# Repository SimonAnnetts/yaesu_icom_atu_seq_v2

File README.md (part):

# Yaesu/Icom ATU Sequencer v2

An Arduino Mega 2560 controller that:

- interfaces an **Icom AH-4-type ATU** (or any tuner using the same protocol) to
  a **Yaesu FT-847**. Note: the radio's own [TUNER] button is not used - we have our own button that initiates a tuning cycle and keys the radio as necessary;
- provides **three sequencer outputs per band, for four bands** (HF, 50, 144
  and 430MHz), for preamp and power-amp control;
- provides an **ALC output** that can control the radio's power during the
  tune cycle;
- allows complex **inter-band sequencer and tuner configurations** be defined in
  a **JSON config**;
- allows a **PC control of the radio over CAT**, with none of the tuner and
  sequencer operations getting in the way.

## Aims in detail

1. **Use an Icom AH-4-type ATU with the Yaesu FT-847** (or any tuner that
   speaks the same START/KEY protocol, and possibly other Yaesu radios of the
   same era). 
   The FT-847 has no way to drive such a tuner on its own. At the
   press of the TUNE button the Arduino runs the whole
   cycle: it sets the radio up over CAT (tune mode, keying PTT at the right
   moment), drives the tuner's START/KEY lines, watches for it to finish, and
   puts the radio back as it found it. Proven on an Alinco EDX-2, an
   Icom-compatible tuner. **This does not re-purpose the radio's own [TUNER]
   key** or any of its built-in tuner control: the TUNE button is button 
   fitted to this device (with its own tune indicator), and
   the radio's rear TUNER connector is used only for the TX INHIBIT line and
   its supply and ground. Its tuner-sense pin is deliberately left
   unconnected, so the radio never believes a tuner is attached and CAT keeps
   working.
2. **Provide three sequencer outputs per band, for four bands** (HF, 50, 144
   and 430MHz): `SEQ1`–`SEQ3` opto-isolated outputs for preamp and power-amp
   relays, plus `RX`/`TX` indicator LEDs, driven from the radio's STBY jack,
   with a shared **TX INHIBIT** line that holds off the transmitter until
   each band's sequence has finished settling.
3. **Provide an ALC output that can control the radio's power during the tune
   cycle.** A charge pump makes about -4V, gated by an opto-isolator onto the
   radio's EXT ALC jack, so the carrier is held at what the tuner wants (an
   AH-4 needs about 10W). On the prototype one fixed ALC voltage holds the
   FT-847 between 5 and 10W on every band (once the pump is fed from a
   regulator: see below). YMMV - the Yaesu FT-847 ALC circuit, and the power
   levels it produces, are 'unpredictable' at best! The ALC output is **part
   of every tune by default** (it does no harm if the radio's ALC jack isn't
   connected), and can be switched off per band with `"alc": false` in the JSON
   config.
4. **Allow complex inter-band sequencer and tuner configurations to be defined
   in a JSON config**: per-band delays, tune profiles, band edges, which bands
   the tuner may be used on, and cross-band rules (for example, transmitting
   on 50MHz switches off a 144MHz masthead preamp). The config is uploaded
   over USB, validated, and kept in EEPROM; a bad one can never leave the
   sequencer unable to run.
5. **Still let a PC control the radio over CAT, with none of the above getting
   in the way.** The Arduino sits between the PC and the radio and passes CAT
   traffic through byte for byte. While a tune cycle needs the radio, the PC
   keeps being answered (from a snapshot of the radio, with the original mode
   and no PTT), so it cannot tell a tune is happening.

**The PC is optional.** With no PC connected at all, the tune button, the
tuner and the sequencer all work exactly the same way. Standalone operation is
a first-class requirement, not a side effect.

## How it fits together

```
 PC (flrig etc.) ── Port 1 ──┐                        ┌── CAT ── Port 2 ── FT-847
                             │                        │
                       Arduino Mega 2560 ─────────────┼── STBY jack (4 bands in)
                             │                        ├── TUNER connector: TX INHIBIT out
   tune button ──────────────┤                        └── EXT ALC jack  ←── charge pump + gate
   tune buzzer ──────────────┤
   AH-4-type ATU ─ START/KEY ┤        12 opto outputs (SEQ1-SEQ3 × 4 bands) + RX/TX LEDs
                             └── USB (Serial0): logging, bench keys, JSON config upload
```

The CAT proxy is the *means*, not the goal: it is what lets aims 1 and 5 hold
at the same time (the tune cycle needs the radio's CAT port while the PC is
still using it). The sequencer (aim 2) does not use CAT at all — it runs from
the STBY lines, so it works with the CAT link absent.

Where to look in this document: [Hardware](#hardware) and the
[Pin plan](#pin-plan-mega-2560) for the wiring; [Behaviour](#behaviour) for the tune
cycle, the sequencer and the config; the reference sections for the
[FT-847 CAT protocol](#yaesu-ft-847-cat-protocol-reference), the [AH-4 interface](#icom-ah-4-atu-interface-reference), the
[ALC circuit](#alc-injection-for-tune-power-reference) and the
[STBY jack, TUNER port and TX INHIBIT](#stby-jack-tuner-port-and-tx-inhibit-reference); [Bench results](#bench-results)
for what has been verified on the real radio and tuner; [Open
questions](#open-questions--to-be-determined) for what has not.

## Hardware

- **Arduino Mega 2560** as the controller.
- **Serial0 (USB)**: connected to a PC via USB, used for debugging/logging and
  local control/monitoring of the Arduino itself. Not part of the CAT path.
- **Serial2 ("Port 1")**: connects to the PC's CAT serial port, via one half
  of a MAX202CPE (RS-232 level shifter).
- **Serial3 ("Port 2")**: connects to the Yaesu FT-847's CAT port, via the
  other half of the MAX202CPE.
- **Serial1**: unused, left entirely free — see [pin plan](#pin-plan-mega-2560) below.
- **Icom ATU interface**: drives an Icom-series automatic antenna tuner (e.g.
  AH-4) using its start/key line(s) and tune-complete signalling.
- **Tune button**: a new, separate physical pushbutton added by this device,
  wired to an Arduino input, used to initiate a tune cycle. It has nothing to
  do with the radio's front-panel [TUNER] key, which is not used or
  intercepted.
- **ALC injection circuit**: a charge pump driven from an Arduino PWM pin
  (producing roughly -4V), gated onto the radio's ALC line through an
  opto-isolator used purely as a switch. This lets the Arduino trim the
  radio's RF output to the ~10W carrier the AH-4 wants during a tune cycle
  (it aborts outside 5–15W — see the [AH-4 reference](#icom-ah-4-atu-interface-reference) below), independent
  of — and in addition to — the AM-mode power ceiling (see below). Carried over from a prior project; confirmed against the FT-847
  manual — see the [ALC reference section](#alc-injection-for-tune-power-reference) further down.
- **Amplifier sequencer**: 4 independent relay sequencers, one per band —
  Band 1=HF, Band 2=50MHz, Band 3=144MHz, Band 4=430MHz — each with 5
  distinct outputs —
  `RX`, `SEQ1`, `SEQ2`, `SEQ3`, `TX`. These are cumulative, not mutually
  exclusive: `SEQ1`-`SEQ3` latch on in order and stay on together for the
  whole transmission, while `RX`/`TX` are boundary-condition indicator
  LEDs (see [Sequencer](#sequencer) under [Behaviour](#behaviour) for the exact timing). All 5 drive
  a status LED; only `SEQ1`/`SEQ2`/`SEQ3` also drive an opto-isolator
  (`RX`/`TX` are LED indicators only, no relay/opto function) — 12
  opto-isolator outputs total, 3 per band (see [Pin plan](#pin-plan-mega-2560)). Triggered by the
  radio's STBY jack (4 closure-to-ground T/R lines, wired to the
  interrupt-capable pins — see [Pin plan](#pin-plan-mega-2560)). A single, shared **TX INHIBIT**
  output (D4) holds off the radio's actual transmit output while each
  band's sequence runs, wired to pin 8 of the radio's TUNER connector.
  Also configurable (JSON-based — see below) so that transmitting on one
  band can partially trigger another band's sequencer, e.g. disabling a
  masthead preamp on an unrelated band while transmitting nearby. See
  [Sequencer](#sequencer) under [Behaviour](#behaviour), and the [TUNER-port reference
  section](#stby-jack-tuner-port-and-tx-inhibit-reference) further down for the confirmed pinout and how the CAT-disable
  risk is avoided (by deliberately leaving the TUNER connector's separate
  Tuner Sense pin unconnected).

### Pin plan (Mega 2560)

| Pin(s) | Function |
|---|---|
| D0/D1 (Serial0) | USB debug/control link to PC |
| D16/D17 (Serial2) | Port 1 — CAT to PC, via MAX202CPE |
| D14/D15 (Serial3) | Port 2 — CAT to radio, via MAX202CPE |
| D6 | Tune button (input, polled) |
| D7 | Tune indicator: passive buzzer, ~2048Hz PWM from Timer4 (OC4B) |
| D8 | CAT activity LED (output): lit for 20ms after every byte on either CAT port - the PC's, the radio's, and the Arduino's own commands and replies |
| D9 | ALC injection charge pump (PWM output, Timer2) |
| D10 | ALC opto-isolator LED drive (the "gate"): a plain on/off switch |
| D11 | Icom AH-4 `KEY` input, via opto-isolator, `INPUT_PULLUP` |
| D12 | Icom AH-4 `START` output, via opto-isolator |
| D2 | STBY: HF (input, interrupt) |
| D3 | STBY: 430MHz (input, interrupt) |
| D18 | STBY: 144MHz (input, interrupt) |
| D19 | STBY: 50MHz (input, interrupt) |
| D4 | Shared TX INHIBIT output → TUNER connector pin 8 |
| D34 / D35 / D36 / D37 / D38 | Sequencer Band 1 (**HF**): `RX` (LED only) / `SEQ1` (LED+opto) / `SEQ2` (LED+opto) / `SEQ3` (LED+opto) / `TX` (LED only) |
| D39 / D40 / D41 / D42 / D43 | Sequencer Band 2 (**50MHz**): `RX` / `SEQ1` / `SEQ2` / `SEQ3` / `TX` — same LED-only/LED+opto pattern as Band 1 |
| D44 / D45 / D46 / D47 / D48 | Sequencer Band 3 (**144MHz**): `RX` / `SEQ1` / `SEQ2` / `SEQ3` / `TX` — same pattern |
| D49 / D50 / D51 / D52 / D53 | Sequencer Band 4 (**430MHz**): `RX` / `SEQ1` / `SEQ2` / `SEQ3` / `TX` — same pattern; D50-D53 are the Mega's hardware SPI pins (MISO/MOSI/SCK/SS), repurposed as plain digital outputs since SPI isn't needed elsewhere in this project |
| D5, D22–D33 | **unassigned** — free (D5 was once reserved for the TUNER connector's `TX_GND`, which is not connected; the sequencer outputs occupy D34–D53 as one contiguous block) |
| D20, D21 (I2C: SDA/SCL) | **kept free** — not used by anything, available for a future I2C peripheral (e.g. a status display) |

Sequencer band↔channel mapping (Band 1=HF, Band 2=50MHz, Band 3=144MHz,
Band 4=430MHz) is independent of, and doesn't follow the same order as,
the STBY input pin assignment above (D2=HF, D3=430MHz, D18=144MHz,
D19=50MHz) — each STBY input simply needs to be cross-wired in firmware
to drive its matching band's sequencer channel, e.g. STBY D2 (HF) drives
Band 1 (D34-38), STBY D3 (430MHz) drives Band 4 (D49-53), and so on.

Only six Mega 2560 pins support true external interrupts: D2, D3, D18,
D19, D20, D21. Putting both CAT links on Serial2/Serial3 (rather than
Serial1) means Serial1's pins — D18/D19, which are two of those six
interrupt-capable pins — are never touched, so **all six** interrupt pins
stay free instead of just four. Four of them (D2, D3, D18, D19) are now
used for the 4 STBY band lines (interrupt-driven, since a TX request
needs to be caught immediately to start the sequencer); the remaining two
(D20/D21) stay free of any reservation for I2C. The tune button (D6)
doesn't need an interrupt-capable pin — it's polled in the main loop — so
it and the two status LEDs (D7, D8) sit comfortably outside the reserved
set. The 20 sequencer outputs (D34-D53) and the shared TX INHIBIT output
(D4) are plain digital outputs with no special pin requirements. The
Arduino-side band↔pin mapping for STBY (which of D2/D3/D18/D19
is HF vs 50 vs 144 vs 430) is likewise our own software's choice; what
actually matters is wiring it consistently against the STBY jack's real
per-band wiring (see the [STBY jack reference](#stby-jack-tuner-port-and-tx-inhibit-reference) below).

## Behaviour

### Normal operation (passthrough)

- Bytes arriving on Port 1 (from the PC) are forwarded to Port 2 (to the
  radio), and bytes arriving on Port 2 (from the radio) are forwarded to
  Port 1 (to the PC).
- If no PC is connected, Port 1 simply carries no traffic — there is
  nothing to relay. This is a normal, fully supported state, not an error
  condition; see [Standalone operation](#standalone-operation) below for how the tune cycle still
  works correctly in this case.
- **Power-up resync.** When the Arduino powers up it puts a glitch on the
  radio's serial line (the RS-232 level shifter comes up), which can leave the
  radio's CAT port with CAT off, or with its 5-byte parser out of step by one
  stray byte. flrig's polls arrive back to back, so the radio never gets the
  200ms gap it needs to resync and then never answers (flrig shows no
  communication until Init). So for the first ~0.5s the bridge holds the PC's
  bytes unread in the serial buffer (nothing is lost: it holds about 50
  frames), lets the bus go quiet for 300ms, sends one CAT on, waits 200ms for the
  radio to settle, and only then starts forwarding — the held polls go through
  intact and in order, so the only visible effect is flrig's first answer
  arriving about half a second after power-up. A tune requested in that
  window waits for it. CAT on is idempotent, so a healthy radio is unaffected;
  with the radio off nothing answers and the bridge simply carries on.

### What actually needs faking during a tune cycle

The tune cycle only ever changes two things about the radio's externally
visible state: **mode** (forced to AM) and **PTT/TX status** (forced on).
Frequency doesn't change; CTCSS/DCS/satellite-toggle/etc. don't change;
none of it is touched by tuning. That means the Arduino only ever needs to
fake two specific things, not maintain a general-purpose cache of
"everything the PC might ask":

- **Mode** — the mode byte within the `Get freq+mode, Main` reply
  (opcode `0x03`; see the [CAT reference](#yaesu-ft-847-cat-protocol-reference) below). This reply packs
  frequency and mode into one 5-byte frame, so the Arduino must splice the
  *real, live* frequency (queried from the radio, since it's genuinely
  unchanged) together with the *faked* pre-tune mode byte — not fake the
  whole response.
- **PTT/TX status** — the PTT bit in the `Get TX status` reply
  (opcode `0xF7`).
- Nothing else needs faking. In particular, RX status/S-meter (opcode
  `0xE7`) can be forwarded live and truthfully even while keyed — a
  receiver being blind during any transmission (including an entirely
  ordinary, manually-initiated one) is unremarkable and gives nothing
  away.
- **Any CAT query the Arduino doesn't specifically recognise is simply
  forwarded to the radio and its response forwarded back, live, even
  during a tune cycle.** There is no cache-completeness problem to solve —
  a query the Arduino has never seen before isn't one it needs to fake an
  answer for, because the radio itself can truthfully answer it regardless
  of whether it's mid-tune. Pre-populating an exhaustive cache of "every
  possible CAT parameter" is unnecessary; only the two items above ever
  diverge from the truth.

### Tune cycle (triggered by the tune button)

The tune cycle must also drive the amplifier sequencer for whichever band
it's about to transmit on — a tune cycle keys PTT just like any other
transmission, and the sequencer's relay chain has to be up before RF
appears, exactly as it would for a normal transmission.

A CAT-commanded PTT does assert the radio's STBY line(s) (bench-verified —
see [Bench results](#bench-results) below), but the lead time before RF is still unmeasured.
Rather than depend on that, the tune cycle **explicitly drives the
sequencer itself**, calling the same up/down-sequence logic the STBY
interrupt handler uses, directly and proactively:

1. Actively query the radio's current mode and frequency over CAT
   (`Get freq+mode, Main`, opcode `0x03`) and note the current PTT/TX
   status is "off" (this is always known without needing to ask, since
   the Arduino is the one about to turn it on). This captures the values
   that will need to be faked and restored, freshly, at the start of
   every cycle — so it works identically whether or not a PC (and any
   snooped history) exists.
2. Map that frequency to one of the 4 sequencer bands (see [Sequencer
   configuration](#sequencer-configuration-and-cross-band-triggers) below — band edges live in the same JSON config).
3. **Explicitly run that band's *tune* profile up-sequence first, before
   touching the AH-4 at all** — assert TX INHIBIT, step through whichever
   stages the tune profile includes for this band (may stop at `SEQ2`,
   skipping `SEQ3` — see "Two profiles per band" under [Sequencer](#sequencer) above),
   release TX INHIBIT — using the same function the STBY interrupt handler
   calls, but with the tune profile rather than the normal-TX profile.
   - **This band's STBY interrupt handling must be suppressed for the
     duration of the tune cycle.** The idempotency argument used elsewhere
     (calling "run up-sequence" again on an already-sequenced band is a
     harmless no-op) only holds when both callers agree on the same
     profile. Here they don't: if the radio's own STBY line asserts once
     PTT goes active and the interrupt handler fires using the *normal*
     profile, it would engage `SEQ3` anyway — exactly what the tune
     profile exists to prevent. So the tune cycle needs to mark this band
     as "under explicit tune-profile control" and have the STBY handler
     defer to it (skip its own trigger) until the tune cycle releases
     that band again in step 9.
   - **Ordering also matters here**: this step is deliberately done
     *before* issuing the AH-4 `START` signal (step 5), not interleaved
     with it.
     The AH-4 has its own tight timing — it asserts `KEY` about 300ms
     after `START`, then expects the carrier almost immediately so it can
     check the power — and the sequencer's relay-settling delay is
     user-configurable and could easily be longer than that. Running the
     sequencer to completion first, while the radio is still fully idle,
     keeps that variable delay out of the AH-4's time-sensitive window
     entirely, so `START → KEY → PTT-key → RF appears` stays a tight,
     undisturbed sequence exactly as the AH-4 expects.
4. Take over the CAT link to the radio and select AM mode (there is no CAT
   power-set command on this radio — switching to AM mode is itself the
   main power reduction, since the FT-847 caps AM output much lower than
   SSB/CW/FM; see the [CAT reference](#yaesu-ft-847-cat-protocol-reference) below). **The target is about 10W, not
   the minimum:** the AH-4 measures the carrier during the tune and aborts
   if it is outside 5–15W (see the [AH-4 reference](#icom-ah-4-atu-interface-reference) below). AM mode alone
   still allows up to 25W on HF, so the radio's RF power setting and/or the
   ALC injection circuit must bring the carrier into that window. ALC
   injection is on by default for every band (the config's per-band `alc`
   flag can turn it off, and the no-RF test modes never use it): it is applied
   right after the mode is set — the gate switches the charge pump's -4V onto
   the radio's ALC line and is given 100ms to settle — before `START` and
   before the radio is keyed (see [ALC in the firmware](#alc-in-the-firmware-srcalc_ioh)).
   Also claim the CAT bus now (hold PC traffic) so that PTT can go out the
   instant `KEY` asserts, rather than queueing behind a PC poll.
5. Assert `START` (pull it low via its opto), hold it for about 560ms like
   an Icom radio does, then release it. **Key the radio's PTT via CAT right
   away, at `START`, not later at `KEY`.** The radio's carrier overshoots to
   2–3× its set power for ~0.7s after keying and an Alinco EDX-2 that is only
   given RF at `KEY` measures that overshoot, gives up after ≈350ms and
   leaves the SWR >3:1; keyed at `START` the carrier has settled by the time
   `KEY` asserts (≈590ms) and the tune runs 3–4s and ends near 1:1. The cost
   is a few hundred ms of carrier into the unmatched antenna before `KEY`,
   which is acceptable at ~10W (a genuine AH-4 would route RF through its
   power divider only after `KEY`; the key-on-`KEY` variant, Serial0 `R`, is
   kept for tuners that need that). Meanwhile, continue forwarding any other
   CAT traffic between PC and radio live (see above) — only mode and PTT/TX
   status queries get answered from the values captured in step 1 instead
   of the truth.
6. Wait for the tuner to assert `KEY` (during the `START` hold on a genuine
   AH-4, ~35ms after `START` is released on the Alinco EDX-2); give up as
   "no ATU" if it never does (and unkey).
7. Wait for the ATU to signal that its tune cycle has completed: `KEY`
   releasing and staying released is success; `KEY` releasing for ~20ms,
   re-asserting for ~200ms, then releasing is the AH-4's "not tuned"
   signal. (A short `KEY` is not necessarily a failure: an EDX-2 with a
   stored match for the frequency finishes quickly, and the match only
   shows in the SWR on the next key-up. The log shows how long `KEY` was
   asserted; the real judge is the SWR afterwards.)
8. Unkey the radio's PTT **immediately on `KEY`'s first release** (the
   tuner never switches its relays under power, and an Icom radio stops
   transmitting the moment `KEY` goes away). If ALC injection is on, its
   gate is released as soon as the radio is unkeyed.
9. Restore the radio's original mode (from the value captured in step 1;
   retried up to 3 times, and a failure is reported loudly on Serial0), then
   release the CAT bus so PC traffic can flow again.
10. **Explicitly run that band's *tune* profile down-sequence** — the
    mirror of step 3, stepping down through whatever stages the tune
    profile actually engaged. Once complete, release this band from
    "under explicit tune-profile control" so its STBY interrupt handling
    resumes normally.
11. Resume normal passthrough with no faking.

#### Implementation notes (`src/tune.h`, `src/tune_io.cpp`)

- **One tail for every outcome.** Success, refusal, failure, button abort and
  the 30s watchdog all unwind through the same tail — PTT off (retried until
  the radio has been told), restore mode, release the bus, sequencer down,
  drop the STBY hold, wait for START to finish its hold — so no path can
  skip a cleanup step. It is a pure state machine tested against a fake
  radio and a fake tuner (both an EDX-2-style and a genuine-AH-4-style
  timing) with failures injected at every step and an abort swept across the
  whole cycle.
- **The cycle owns the CAT bus** from before `START` until the restore: the
  arbiter's claim lets PTT go out without queueing behind PC traffic. The PC
  is not locked out meanwhile — it is answered from a snapshot (see [PC
  transparency during a tune cycle](#pc-transparency-during-a-tune-cycle)). A claim also releases itself after 60s
  so the PC can never be locked out.
- **ALC injection is part of the cycle, on by default.** When the tuned band's
  config has `alc` on (the default), the cycle has an extra `Alc` step between
  setting the mode and starting the tuner, and releases the gate in the tail
  right after PTT off on every path (tested: never left on after a failure, an
  abort at any moment, or a stuck PTT off). The radio does not currently
  respond to the ALC voltage, so for now it changes nothing, and the tune does
  not depend on it.
- **A radio that does not answer is woken up, not given up on at once.** After
  the Arduino itself has been power-cycled the radio may stop answering CAT (its
  CAT is off, or its 5-byte parser has been left out of step by a stray byte, and
  a PC polling back to back never gives it the 200ms gap it needs to resync). flrig
  then shows no communication until Init, and the tune button used to fail with
  "could not claim the CAT bus" (the PC's polls of the silent radio kept the bus
  looking busy). Now the claim succeeds, and if the first status query gets no
  answer the cycle goes quiet for 300ms, sends CAT on again, lets the radio settle
  for 200ms and asks again, twice, before failing with "CAT query failed". The
  normal path is unchanged (one CAT on, straight to the queries). A successful
  tune leaves the radio's parser aligned, so flrig recovers too.
- **Refusals** (nothing is left changed): a band already transmitting, the
  radio reporting it is transmitting, a frequency in no band, a band the AH-4
  isn't enabled for (the config's per-band `atu` flag), no usable
  answer to a CAT query (including a mode byte that couldn't be restored).
- **CAT activity LED (D8):** lights for 20ms after every byte seen on either CAT
  port, so it flickers with flrig's polling and glows steadily when traffic is
  dense. It counts the PC's bytes (forwarded to the radio, or read while a tune
  has the radio), the radio's bytes (forwarded to the PC, or replies to the
  Arduino's own commands, or strays), the Arduino's own commands, commands
  replayed after a tune, and the recovery commands sent at boot - so a
  standalone tune with no PC still lights it. It is off at boot and with no
  traffic, and the walk-test's `ACTIVITY_LED` step drives it directly.
- **Tune indicator (D7, a passive buzzer):** driven at ~2048Hz by Timer4's
  hardware PWM (not `tone()`, which would take Timer2 from the ALC pump). A
  continuous tone while a cycle runs; three slow beeps on success; fast
  beeping for about a second on failure or refusal; silent after an abort.
  A low-resistance magnetic buzzer must not be driven straight from the pin
  (a 40Ω coil would draw ~125mA against the Mega's 40mA absolute maximum): put
  about **330Ω** in series (~13mA peak, moderate volume; 1kΩ is very quiet,
  not below ~220Ω), optionally a 1N4148 across the buzzer (cathode to the
  pin side), or use a transistor for more volume. `BUZZER_DUTY_PERCENT` in
  `src/buzzer.cpp` is a software volume control.
- **Controls:** the tune button starts a full tune and, pressed during one,
  aborts it. Serial0 keys: `T` full tune, `E` ATU handshake with the radio
  *not* keyed, `D` dry run (sequencer and AM mode only — no ATU, no RF), `M`
  full tune that also logs the radio's PO/ALC meter (about every 60ms while
  keyed; a diagnostic that can delay PTT off by up to ~100ms, so use it at low
  power only), `P` carrier test (keys the radio for 2s with *no* tuner and
  logs the meter — shows the radio's own start-up behaviour on its own), `R`
  full tune that keys the radio at `START` instead of at `KEY` (so the radio's
  start-up overshoot, below, has settled before the tuner measures), `1`/`2`/`3`
  tune mode AM/FM/CW (default AM), `X` abort. The FT-847 cannot report SWR over CAT, and its status byte is a
  5-bit bar-graph value (not calibrated watts), so SWR and real power need
  external meters.
- **Staged bench procedure** (dummy load, low power): `D` first (check the
  sequencer steps up with the tune profile, the radio goes to AM and comes
  back), then `E` (START/KEY with the real tuner but no carrier — expect "not
  a real tune"), then `T` into a dummy load with the radio's power set for
  about 10W, then onto the antenna.

### Reset safety (watchdog and crash recovery)

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
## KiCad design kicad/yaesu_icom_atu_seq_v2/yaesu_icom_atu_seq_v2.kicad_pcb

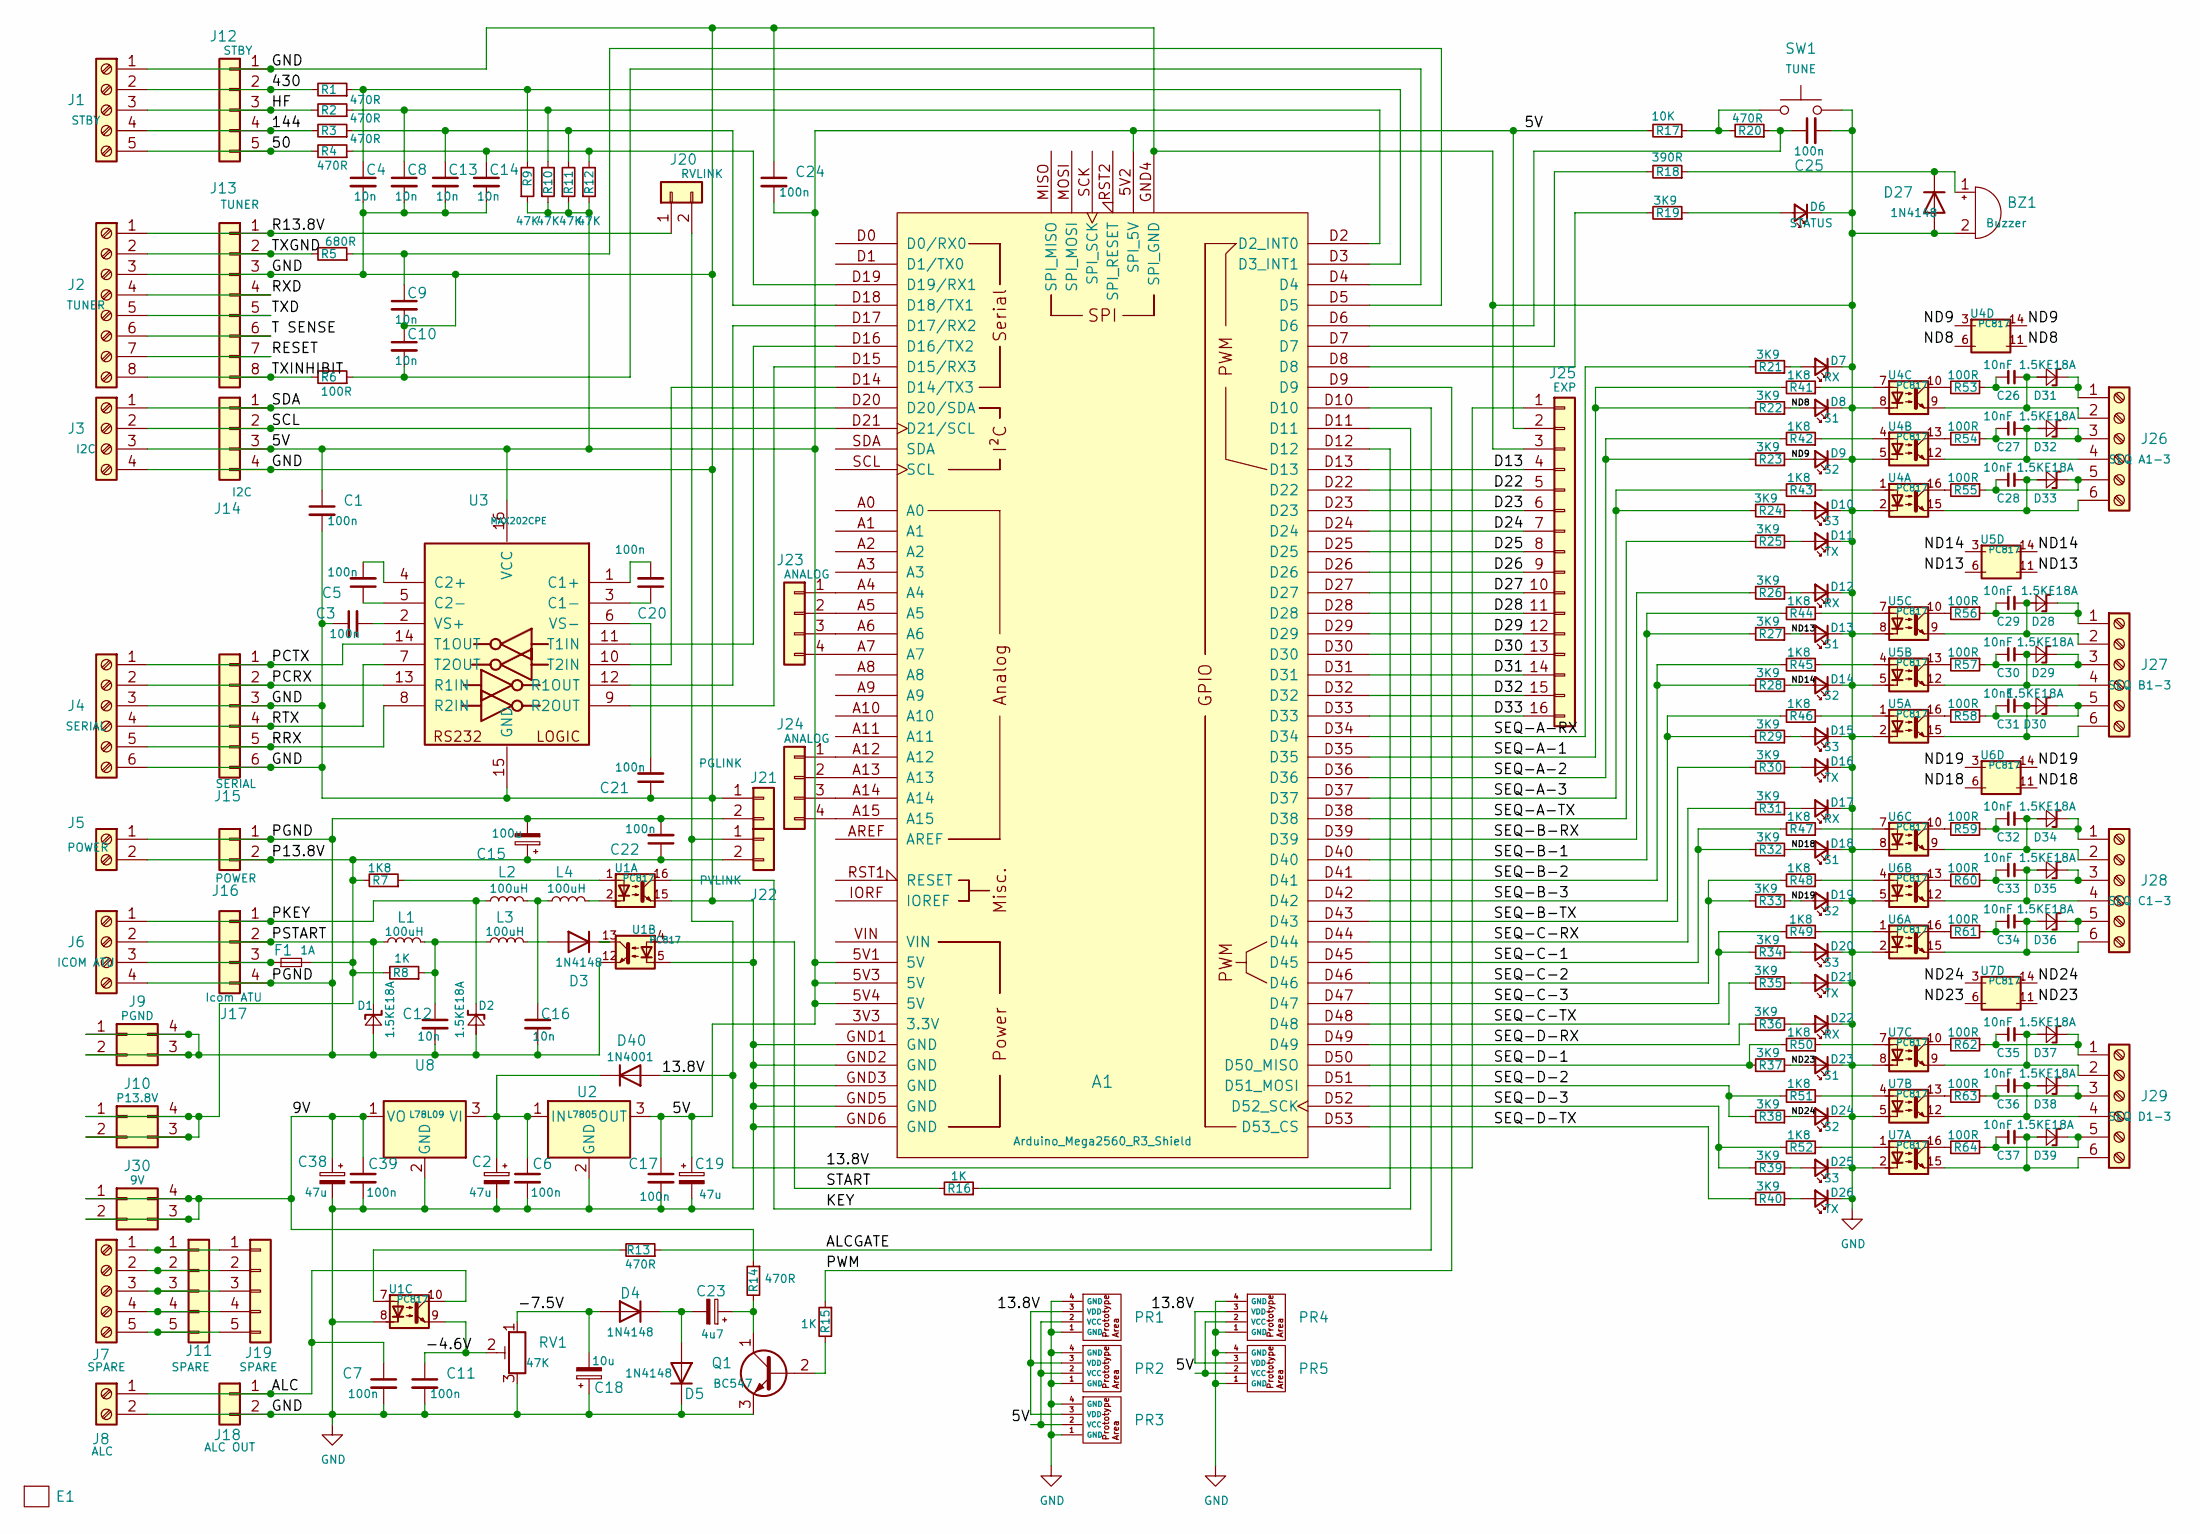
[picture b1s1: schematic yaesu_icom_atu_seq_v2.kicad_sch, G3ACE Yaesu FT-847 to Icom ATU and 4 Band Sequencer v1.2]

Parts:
A1: Arduino_Mega2560_R3_Shield
BZ1: Buzzer; Buzzer_12x9.5RM7.6
C1, C3, C5, C6, C7, C11, C17, C20, C21, C22, C24, C25, C39: 100n; C_Disc_D4.3mm_W1.9mm_P5.00mm
C2, C19, C38: 47u; CP_Radial_D5.0mm_P2.50mm
C4, C8, C9, C10, C12, C13, C14, C16: 10n; C_Disc_D4.3mm_W1.9mm_P5.00mm
C15: 100u; CP_Radial_D5.0mm_P2.50mm
C18: 10u; CP_Radial_D5.0mm_P2.50mm
C23: 4u7; CP_Radial_D5.0mm_P2.50mm
C26, C27, C28, C29, C30, C31, C32, C33, C34, C35, C36, C37: 10nF; C_Disc_D5.1mm_W3.2mm_P5.00mm
D1, D2, D28, D29, D30, D31, D32, D33, D34, D35, D36, D37, D38, D39: 1.5KE18A; D_DO-201AE_P15.24mm_Horizontal
D3, D4, D5, D27: 1N4148; D_DO-35_SOD27_P7.62mm_Horizontal
D6: STATUS; LED_THT_L72CB_Kingbright
D7, D12, D17, D22: RX; LED_THT_L72CB_Kingbright
D8, D13, D18, D23: S1; LED_THT_L72CB_Kingbright
D9, D14, D19, D24: S2; LED_THT_L72CB_Kingbright
D10, D15, D20, D25: S3; LED_THT_L72CB_Kingbright
D11, D16, D21, D26: TX; LED_THT_L72CB_Kingbright
D40: 1N4001; D_DO-35_SOD27_P7.62mm_Horizontal
E1: Hammond_Enclosure_RM2095L
F1: 1A; Fuse_Blade_ATO_directSolder (longer holes)
J1: STBY; TerminalBlock_Phoenix_PT-1,5-5-3.5-H_1x05_P3.50mm_Horizontal
J2: TUNER; TerminalBlock_Phoenix_PT-1,5-8-3.5-H_1x08_P3.50mm_Horizontal
J3: I2C; TerminalBlock_Phoenix_PT-1,5-4-3.5-H_1x04_P3.50mm_Horizontal
J4: SERIAL; TerminalBlock_Phoenix_PT-1,5-6-3.5-H_1x06_P3.50mm_Horizontal
J5: POWER; TerminalBlock_Phoenix_PT-1,5-2-3.5-H_1x02_P3.50mm_Horizontal
J6: ICOM ATU; TerminalBlock_Phoenix_PT-1,5-4-3.5-H_1x04_P3.50mm_Horizontal
J7: SPARE; TerminalBlock_Phoenix_PT-1,5-5-3.5-H_1x05_P3.50mm_Horizontal
J8: ALC; TerminalBlock_Phoenix_PT-1,5-2-3.5-H_1x02_P3.50mm_Horizontal
J9: PGND; PinHeader_2x02_P2.54mm_Vertical
J10: P13.8V; PinHeader_2x02_P2.54mm_Vertical
J11, J19: SPARE; PinHeader_1x05_P2.54mm_Vertical
J12: STBY; PinHeader_1x05_P2.54mm_Vertical
J13: TUNER; PinHeader_1x08_P2.54mm_Vertical
J14: I2C; PinHeader_1x04_P2.54mm_Vertical
J15: SERIAL; PinHeader_1x06_P2.54mm_Vertical
J16: POWER; PinHeader_1x02_P2.54mm_Vertical
J17: Icom ATU; PinHeader_1x04_P2.54mm_Vertical
J18: ALC OUT; PinHeader_1x02_P2.54mm_Vertical
J20: RVLINK; PinHeader_1x02_P2.54mm_Vertical
J21: PGLINK; PinHeader_1x02_P2.54mm_Vertical
J22: PVLINK; PinHeader_1x02_P2.54mm_Vertical
J23, J24: ANALOG; PinHeader_1x04_P2.54mm_Vertical
J25: EXP; PinHeader_1x16_P2.54mm_Vertical
J26: SEQ A1-3; TerminalBlock_Phoenix_PT-1,5-6-3.5-H_1x06_P3.50mm_Horizontal
J27: SEQ B1-3; TerminalBlock_Phoenix_PT-1,5-6-3.5-H_1x06_P3.50mm_Horizontal
J28: SEQ C1-3; TerminalBlock_Phoenix_PT-1,5-6-3.5-H_1x06_P3.50mm_Horizontal
J29: SEQ D1-3; TerminalBlock_Phoenix_PT-1,5-6-3.5-H_1x06_P3.50mm_Horizontal
J30: 9V; PinHeader_2x02_P2.54mm_Vertical
L1, L2, L3, L4: 100uH; L_Axial_L9.5mm_D4.0mm_P5.08mm_Vertical_Fastron_SMCC
PR1, PR2, PR3, PR4, PR5: Prototype Area 5x13 with 4 rails (5x17) 2.54mm Grid
Q1: BC547; TO-92L_Wide
R1, R2, R3, R4, R13, R14, R20: 470R; R_Axial_DIN0207_L6.3mm_D2.5mm_P10.16mm_Horizontal
R5: 680R; R_Axial_DIN0207_L6.3mm_D2.5mm_P10.16mm_Horizontal
R6, R53, R54, R55, R56, R57, R58, R59, R60, R61, R62, R63, R64: 100R; R_Axial_DIN0207_L6.3mm_D2.5mm_P10.16mm_Horizontal
R7, R41, R42, R43, R44, R45, R46, R47, R48, R49, R50, R51, R52: 1K8; R_Axial_DIN0207_L6.3mm_D2.5mm_P10.16mm_Horizontal
R8, R15, R16: 1K; R_Axial_DIN0207_L6.3mm_D2.5mm_P10.16mm_Horizontal
R9, R10, R11, R12: 47K; R_Axial_DIN0207_L6.3mm_D2.5mm_P10.16mm_Horizontal
R17: 10K; R_Axial_DIN0207_L6.3mm_D2.5mm_P10.16mm_Horizontal
R18: 390R; R_Axial_DIN0207_L6.3mm_D2.5mm_P10.16mm_Horizontal
R19, R21, R22, R23, R24, R25, R26, R27, R28, R29, R30, R31, R32, R33, R34, R35, R36, R37, R38, R39, R40: 3K9; R_Axial_DIN0207_L6.3mm_D2.5mm_P10.16mm_Horizontal
RV1: 47K; Potentiometer_Bourns_3296W_Vertical
SW1: TUNE; SW_PUSH-12mm
U1, U4, U5, U6, U7: PC817; 3 x PC817 on a DIP-16_W7.62mm_Socket_LongPads
U2: L7805; TO-220-3_Horizontal_TabDown
U3: MAX202CPE; DIP-16_W7.62mm_Socket_LongPads
U8: L78L09; TO-92_Inline

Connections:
/5V: A1.5V1 (5V), A1.5V2 (SPI_5V), A1.5V3 (5V), A1.5V4 (5V), C1.1, C17.1, C19.1, C24.2, J3.3, J14.3, J25.2, PR1.2 (VCC), PR2.2 (VCC), PR3.2 (VCC), PR4.2 (VCC), PR5.2 (VCC), R9.1, R10.1, R11.1, R12.1, R17.2, U2.3 (OUT), U3.16 (VCC)
/9V: C38.1, C39.1, J30.1, J30.2, J30.3, J30.4, R14.1, U8.1 (VO)
/13.8V: D40.2 (A), J20.2, J22.1, J25.1, PR1.3 (VDD), PR2.3 (VDD), PR3.3 (VDD), PR4.3 (VDD), PR5.3 (VDD)
/50: J1.5, J12.5, R4.2
/144: J1.4, J12.4, R3.2
/430: J1.2, J12.2, R1.2
/-4.6V: C11.1, RV1.2, U1.9
/-7.5V: C18.2, D4.2 (A), RV1.1
/ALC: C7.1, J8.1, J18.1, U1.10
/ALCGATE: A1.D10, R13.1
/D13: A1.D13, J25.4, PR1.30
/D22: A1.D22, J25.5, PR1.29
/D23: A1.D23, J25.6, PR1.28
/D24: A1.D24, J25.7, PR1.27
/D25: A1.D25, J25.8, PR1.26
/D26: A1.D26, J25.9, PR1.25
/D27: A1.D27, J25.10, PR1.24
/D28: A1.D28, J25.11, PR1.23
/D29: A1.D29, J25.12, PR1.22
/D30: A1.D30, J25.13, PR1.21
/D31: A1.D31, J25.14, PR1.20
/D32: A1.D32, J25.15, PR1.19
/D33: A1.D33, J25.16, PR1.18
/HF: J1.3, J12.3, R2.2
/KEY: A1.D11, U1.16
/ND8: D8.2 (A), R22.1, U4.6, U4.11
/ND9: D9.2 (A), R23.1, U4.3, U4.14
/ND13: D13.2 (A), R27.1, U5.6, U5.11
/ND14: D14.2 (A), R28.1, U5.3, U5.14
/ND18: D18.2 (A), R32.1, U6.6, U6.11
/ND19: D19.2 (A), R33.1, U6.3, U6.14
/ND23: D23.2 (A), R37.1, U7.6, U7.11
/ND24: D24.2 (A), R38.1, U7.3, U7.14
/P13.8V: C15.1, C22.1, F1.2, J5.2, J10.1, J10.2, J10.3, J10.4, J16.2, J22.2, R7.2, R8.2
/PCRX: J4.2, J15.2, U3.13 (R1IN)
/PCTX: J4.1, J15.1, U3.14 (T1OUT)
/PGND: C12.2, C15.2, C16.2, C22.2, D1.2 (A2), D2.2 (A2), J5.1, J6.4, J9.1, J9.2, J9.3, J9.4, J16.1, J17.4, J21.2, U1.12
/PKEY: D2.1 (A1), J6.1, J17.1, L2.1
/PSTART: D1.1 (A1), J6.2, J17.2, L1.1
/PWM: A1.D9, R15.1
/R13.8V: J2.1, J13.1, J20.1
/RESET: J2.7, J13.7
/RRX: J4.5, J15.5, U3.8 (R2IN)
/RTX: J4.4, J15.4, U3.7 (T2OUT)
/RXD: J2.4, J13.4
/SCL: A1.D21 (D21/SCL), J3.2, J14.2
/SDA: A1.D20 (D20/SDA), J3.1, J14.1
/SEQ-A-1: A1.D35, R22.2, R41.2
/SEQ-A-2: A1.D36, R23.2, R42.2
/SEQ-A-3: A1.D37, R24.2, R43.2
/SEQ-A-RX: A1.D34, R21.2
/SEQ-A-TX: A1.D38, R25.2
/SEQ-B-1: A1.D40, R27.2, R44.2
/SEQ-B-2: A1.D41, R28.2, R45.2
/SEQ-B-3: A1.D42, R29.2, R46.2
/SEQ-B-RX: A1.D39, R26.2
/SEQ-B-TX: A1.D43, R30.2
/SEQ-C-1: A1.D45, R32.2, R47.2
/SEQ-C-2: A1.D46, R33.2, R48.2
/SEQ-C-3: A1.D47, R34.2, R49.2
/SEQ-C-RX: A1.D44, R31.2
/SEQ-C-TX: A1.D48, R35.2
/SEQ-D-1: A1.D50 (D50_MISO), R37.2, R50.2
/SEQ-D-2: A1.D51 (D51_MOSI), R38.2, R51.2
/SEQ-D-3: A1.D52 (D52_SCK), R39.2, R52.2
/SEQ-D-RX: A1.D49, R36.2
/SEQ-D-TX: A1.D53 (D53_CS), R40.2
/START: R16.2, U1.4
/T SENSE: J2.6, J13.6
/TXD: J2.5, J13.5
/TXGND: J2.2, J13.2, R5.2
/TXINHIBIT: J2.8, J13.8, R6.2
GND: A1.GND1 (GND), A1.GND2 (GND), A1.GND3 (GND), A1.GND4 (SPI_GND), A1.GND5 (GND), A1.GND6 (GND), BZ1.2 (-), C1.2, C2.2, C3.1, C4.2, C6.2, C7.2, C8.2, C9.2, C10.1, C11.2, C13.2, C14.2, C17.2, C18.1, C19.2, C21.1, C24.1, C25.2, C38.2, C39.2, D5.1 (K), D6.1 (K), D7.1 (K), D8.1 (K), D9.1 (K), D10.1 (K), D11.1 (K), D12.1 (K), D13.1 (K), D14.1 (K), D15.1 (K), D16.1 (K), D17.1 (K), D18.1 (K), D19.1 (K), D20.1 (K), D21.1 (K), D22.1 (K), D23.1 (K), D24.1 (K), D25.1 (K), D26.1 (K), D27.2 (A), J1.1, J2.3, J3.4, J4.3, J4.6, J8.2, J12.1, J13.3, J14.4, J15.3, J15.6, J18.2, J21.1, J25.3, PR1.1 (GND), PR1.4 (GND), PR2.1 (GND), PR2.4 (GND), PR3.1 (GND), PR3.4 (GND), PR4.1 (GND), PR4.4 (GND), PR5.1 (GND), PR5.4 (GND), Q1.3 (E), RV1.3, SW1.2, U1.5, U1.8, U1.15, U2.2 (GND), U3.15 (GND), U4.2, U4.5, U4.8, U5.2, U5.5, U5.8, U6.2, U6.5, U6.8, U7.2, U7.5, U7.8, U8.2 (GND)
unnamed: A1.D2 (D2_INT0), C8.1, R2.1, R10.2
unnamed: A1.D3 (D3_INT1), C4.1, R1.1, R9.2
unnamed: A1.D14 (D14/TX3), U3.10 (T2IN)
unnamed: A1.D15 (D15/RX3), U3.9 (R2OUT)
unnamed: A1.D16 (D16/TX2), U3.11 (T1IN)
unnamed: A1.D17 (D17/RX2), U3.12 (R1OUT)
unnamed: A1.D18 (D18/TX1), C13.1, R3.1, R11.2
unnamed: A1.D19 (D19/RX1), C14.1, R4.1, R12.2
unnamed: A1.D4, C10.2, R6.1
unnamed: A1.D5, C9.1, R5.1
unnamed: A1.D6, C25.1, R20.1
unnamed: A1.D7, R18.2
unnamed: A1.D8, R19.2
unnamed: A1.D12, R16.1
unnamed: BZ1.1 (+), D27.1 (K), R18.1
unnamed: C12.1, L1.2, L3.2, R8.1
unnamed: C16.1, L2.2, L4.2
unnamed: D3.2 (A), L3.1
unnamed: D3.1 (K), U1.13
unnamed: C23.2, D4.1 (K), D5.2 (A)
unnamed: D6.2 (A), R19.1
unnamed: D7.2 (A), R21.1
unnamed: D10.2 (A), R24.1
unnamed: D11.2 (A), R25.1
unnamed: D12.2 (A), R26.1
unnamed: D15.2 (A), R29.1
unnamed: D16.2 (A), R30.1
unnamed: D17.2 (A), R31.1
unnamed: D20.2 (A), R34.1
unnamed: D21.2 (A), R35.1
unnamed: D22.2 (A), R36.1
unnamed: D25.2 (A), R39.1
unnamed: D26.2 (A), R40.1
unnamed: C29.2, D28.1 (A1), J27.1, R56.1
unnamed: C29.1, D28.2 (A2), J27.2, U5.9
unnamed: C30.2, D29.1 (A1), J27.3, R57.1
unnamed: C30.1, D29.2 (A2), J27.4, U5.12
unnamed: C31.2, D30.1 (A1), J27.5, R58.1
unnamed: C31.1, D30.2 (A2), J27.6, U5.15
unnamed: C26.2, D31.1 (A1), J26.1, R53.1
unnamed: C26.1, D31.2 (A2), J26.2, U4.9
unnamed: C27.2, D32.1 (A1), J26.3, R54.1
unnamed: C27.1, D32.2 (A2), J26.4, U4.12
unnamed: C28.2, D33.1 (A1), J26.5, R55.1
unnamed: C28.1, D33.2 (A2), J26.6, U4.15
unnamed: C32.2, D34.1 (A1), J28.1, R59.1
unnamed: C32.1, D34.2 (A2), J28.2, U6.9
unnamed: C33.2, D35.1 (A1), J28.3, R60.1
unnamed: C33.1, D35.2 (A2), J28.4, U6.12
unnamed: C34.2, D36.1 (A1), J28.5, R61.1
unnamed: C34.1, D36.2 (A2), J28.6, U6.15
unnamed: C35.2, D37.1 (A1), J29.1, R62.1
unnamed: C35.1, D37.2 (A2), J29.2, U7.9
unnamed: C36.2, D38.1 (A1), J29.3, R63.1
unnamed: C36.1, D38.2 (A2), J29.4, U7.12
unnamed: C37.2, D39.1 (A1), J29.5, R64.1
unnamed: C37.1, D39.2 (A2), J29.6, U7.15
unnamed: C2.1, C6.1, D40.1 (K), U2.1 (IN), U8.3 (VI)
unnamed: J7.1, J11.1, J19.1
unnamed: J7.2, J11.2, J19.2
unnamed: J7.3, J11.3, J19.3
unnamed: J7.4, J11.4, J19.4
unnamed: J7.5, J11.5, J19.5
unnamed: F1.1, J6.3, J17.3
unnamed: A1.A4, J23.1
unnamed: A1.A5, J23.2
unnamed: A1.A6, J23.3
unnamed: A1.A7, J23.4
unnamed: A1.A12, J24.1
unnamed: A1.A13, J24.2
unnamed: A1.A14, J24.3
unnamed: A1.A15, J24.4
unnamed: L4.1, U1.2
unnamed: Q1.2 (B), R15.2
unnamed: C23.1, Q1.1 (C), R14.2
unnamed: R7.1, U1.1
unnamed: R13.2, U1.7
unnamed: R17.1, R20.2, SW1.1
unnamed: R41.1, U4.7
unnamed: R42.1, U4.4
unnamed: R43.1, U4.1
unnamed: R44.1, U5.7
unnamed: R45.1, U5.4
unnamed: R46.1, U5.1
unnamed: R47.1, U6.7
unnamed: R48.1, U6.4
unnamed: R49.1, U6.1
unnamed: R50.1, U7.7
unnamed: R51.1, U7.4
unnamed: R52.1, U7.1
unnamed: R53.2, U4.10
unnamed: R54.2, U4.13
unnamed: R55.2, U4.16
unnamed: R56.2, U5.10
unnamed: R57.2, U5.13
unnamed: R58.2, U5.16
unnamed: R59.2, U6.10
unnamed: R60.2, U6.13
unnamed: R61.2, U6.16
unnamed: R62.2, U7.10
unnamed: R63.2, U7.13
unnamed: R64.2, U7.16
unnamed: C20.2, U3.1 (C1+)
unnamed: C20.1, U3.3 (C1-)
unnamed: C5.2, U3.4 (C2+)
unnamed: C5.1, U3.5 (C2-)
unnamed: C3.2, U3.2 (VS+)
unnamed: C21.2, U3.6 (VS-)

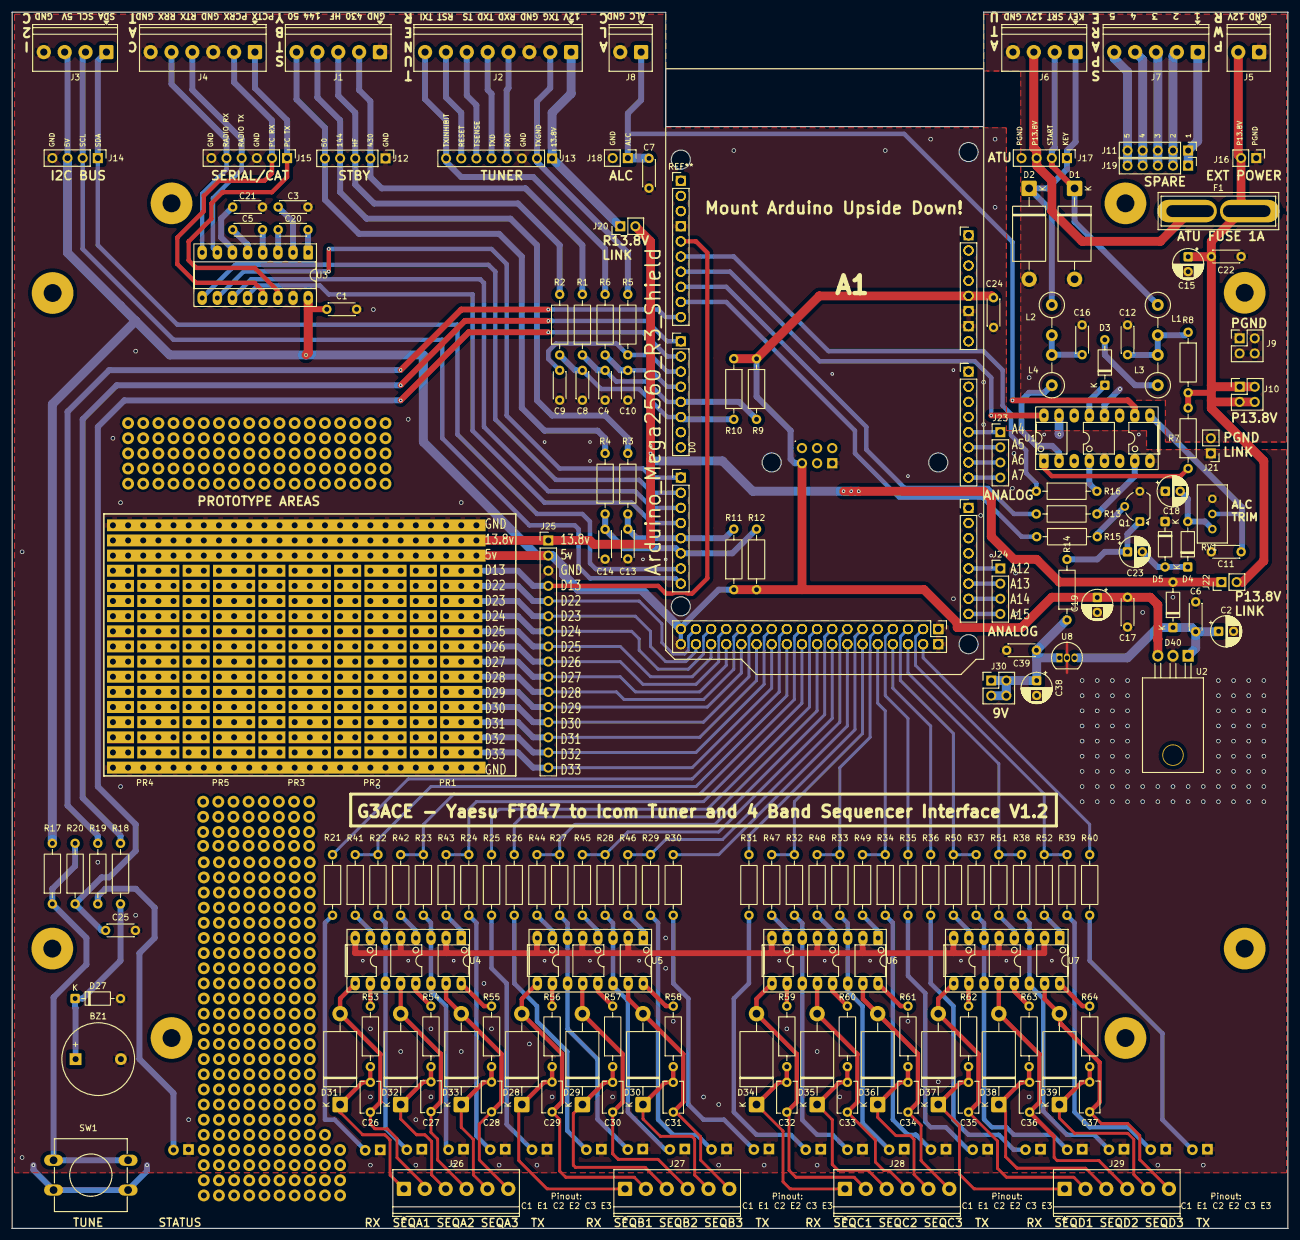
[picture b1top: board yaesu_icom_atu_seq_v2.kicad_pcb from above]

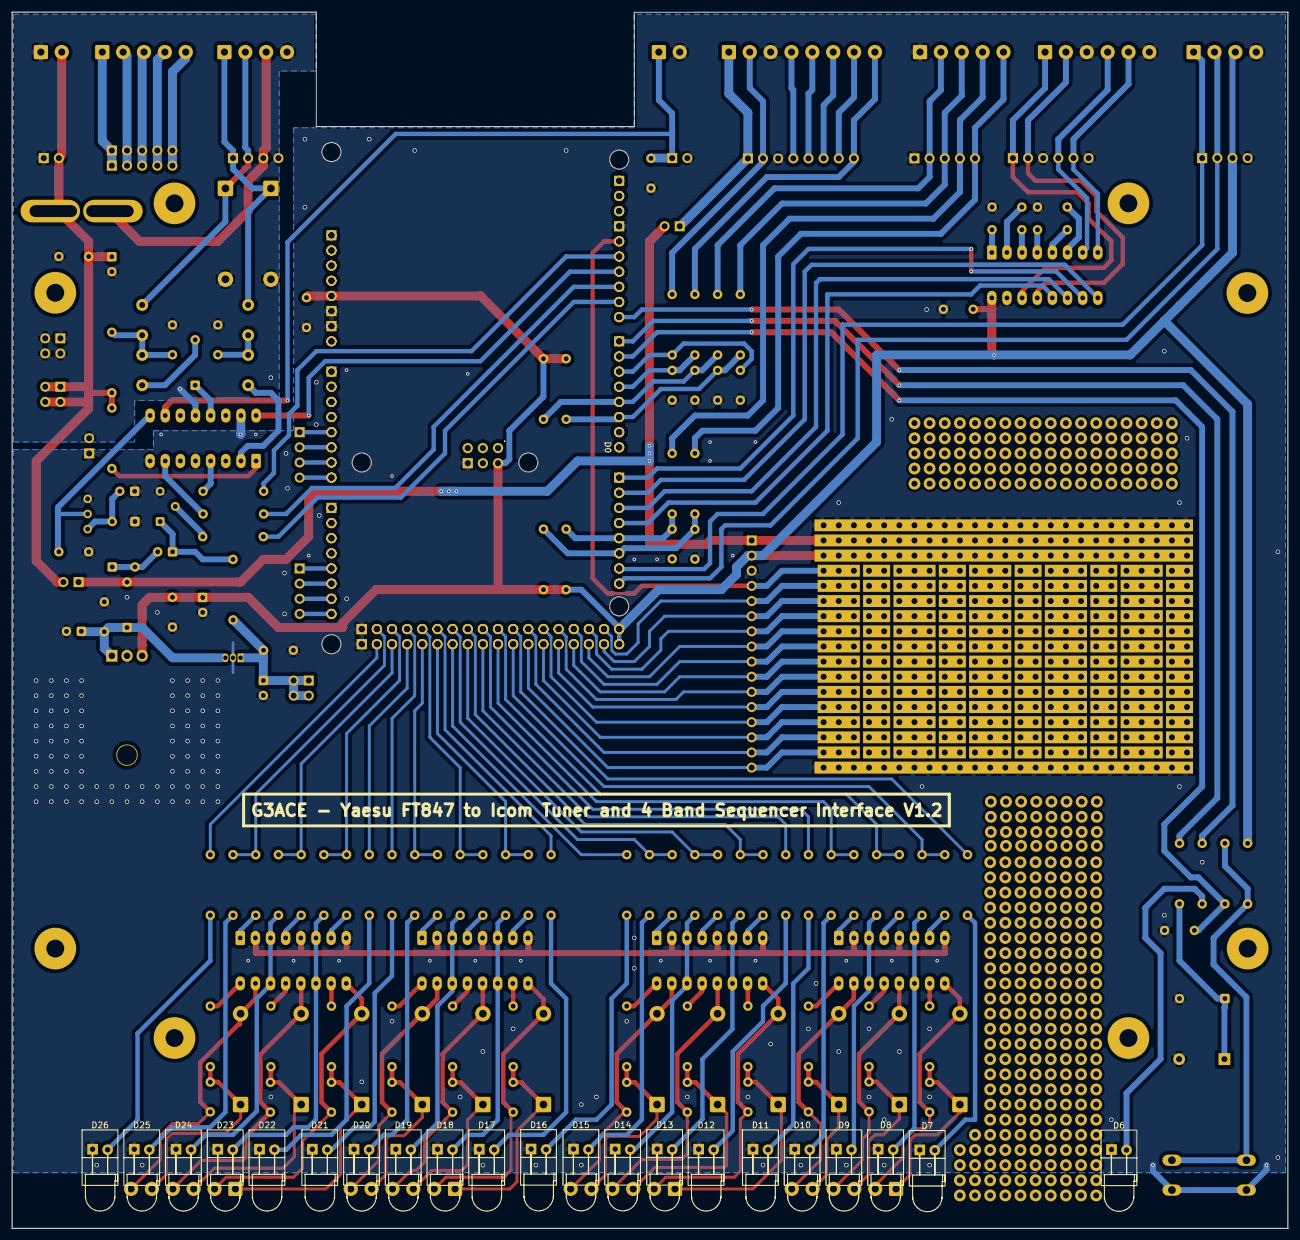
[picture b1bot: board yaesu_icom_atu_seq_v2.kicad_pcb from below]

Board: 2 copper layers, 214.0 x 204.0 mm, 197 parts (22 on the bottom side), 181 nets.

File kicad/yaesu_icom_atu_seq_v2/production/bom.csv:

Designator,Footprint,Quantity,Value,LCSC Part #
A1,Arduino_Mega2560_R3_Shield,1,Arduino_Mega2560_R3_Shield,
BZ1,Buzzer_12x9.5RM7.6,1,Buzzer,
"C1, C11, C17, C20, C21, C22, C24, C25, C3, C39, C5, C6, C7",C_Disc_D4.3mm_W1.9mm_P5.00mm,13,100n,
"C10, C12, C13, C14, C16, C4, C8, C9",C_Disc_D4.3mm_W1.9mm_P5.00mm,8,10n,
C15,CP_Radial_D5.0mm_P2.50mm,1,100u,
C18,CP_Radial_D5.0mm_P2.50mm,1,10u,
"C19, C2, C38",CP_Radial_D5.0mm_P2.50mm,3,47u,
C23,CP_Radial_D5.0mm_P2.50mm,1,4u7,
"C26, C27, C28, C29, C30, C31, C32, C33, C34, C35, C36, C37",C_Disc_D5.1mm_W3.2mm_P5.00mm,12,10nF,
"D1, D2, D28, D29, D30, D31, D32, D33, D34, D35, D36, D37, D38, D39",D_DO-201AE_P15.24mm_Horizontal,14,1.5KE18A,
"D10, D15, D20, D25",LED_THT_L72CB_Kingbright,4,S3,
"D11, D16, D21, D26",LED_THT_L72CB_Kingbright,4,TX,
"D12, D17, D22, D7",LED_THT_L72CB_Kingbright,4,RX,
"D13, D18, D23, D8",LED_THT_L72CB_Kingbright,4,S1,
"D14, D19, D24, D9",LED_THT_L72CB_Kingbright,4,S2,
"D27, D3, D4, D5",D_DO-35_SOD27_P7.62mm_Horizontal,4,1N4148,
D40,D_DO-35_SOD27_P7.62mm_Horizontal,1,1N4001,
D6,LED_THT_L72CB_Kingbright,1,STATUS,
E1,Hammond_Enclosure_RM2095L,1,~,
F1,Fuse_Blade_ATO_directSolder (longer holes),1,1A,
J1,"TerminalBlock_Phoenix_PT-1,5-5-3.5-H_1x05_P3.50mm_Horizontal",1,STBY,
J10,PinHeader_2x02_P2.54mm_Vertical,1,P13.8V,
"J11, J19",PinHeader_1x05_P2.54mm_Vertical,2,SPARE,
J12,PinHeader_1x05_P2.54mm_Vertical,1,STBY,
J13,PinHeader_1x08_P2.54mm_Vertical,1,TUNER,
J14,PinHeader_1x04_P2.54mm_Vertical,1,I2C,
J15,PinHeader_1x06_P2.54mm_Vertical,1,SERIAL,
J16,PinHeader_1x02_P2.54mm_Vertical,1,POWER,
J17,PinHeader_1x04_P2.54mm_Vertical,1,Icom ATU,
J18,PinHeader_1x02_P2.54mm_Vertical,1,ALC OUT,
J2,"TerminalBlock_Phoenix_PT-1,5-8-3.5-H_1x08_P3.50mm_Horizontal",1,TUNER,
J20,PinHeader_1x02_P2.54mm_Vertical,1,RVLINK,
J21,PinHeader_1x02_P2.54mm_Vertical,1,PGLINK,
J22,PinHeader_1x02_P2.54mm_Vertical,1,PVLINK,
"J23, J24",PinHeader_1x04_P2.54mm_Vertical,2,ANALOG,
J25,PinHeader_1x16_P2.54mm_Vertical,1,EXP,
J26,"TerminalBlock_Phoenix_PT-1,5-6-3.5-H_1x06_P3.50mm_Horizontal",1,SEQ A1-3,
J27,"TerminalBlock_Phoenix_PT-1,5-6-3.5-H_1x06_P3.50mm_Horizontal",1,SEQ B1-3,
J28,"TerminalBlock_Phoenix_PT-1,5-6-3.5-H_1x06_P3.50mm_Horizontal",1,SEQ C1-3,
J29,"TerminalBlock_Phoenix_PT-1,5-6-3.5-H_1x06_P3.50mm_Horizontal",1,SEQ D1-3,
J3,"TerminalBlock_Phoenix_PT-1,5-4-3.5-H_1x04_P3.50mm_Horizontal",1,I2C,
J30,PinHeader_2x02_P2.54mm_Vertical,1,9V,
J4,"TerminalBlock_Phoenix_PT-1,5-6-3.5-H_1x06_P3.50mm_Horizontal",1,SERIAL,
J5,"TerminalBlock_Phoenix_PT-1,5-2-3.5-H_1x02_P3.50mm_Horizontal",1,POWER,
J6,"TerminalBlock_Phoenix_PT-1,5-4-3.5-H_1x04_P3.50mm_Horizontal",1,ICOM ATU,
J7,"TerminalBlock_Phoenix_PT-1,5-5-3.5-H_1x05_P3.50mm_Horizontal",1,SPARE,
J8,"TerminalBlock_Phoenix_PT-1,5-2-3.5-H_1x02_P3.50mm_Horizontal",1,ALC,
J9,PinHeader_2x02_P2.54mm_Vertical,1,PGND,
"L1, L2, L3, L4",L_Axial_L9.5mm_D4.0mm_P5.08mm_Vertical_Fastron_SMCC,4,100uH,
"PR1, PR2, PR3, PR4, PR5",Prototype Area 5x13 with 4 rails (5x17) 2.54mm Grid,5,~,
Q1,TO-92L_Wide,1,BC547,
"R1, R13, R14, R2, R20, R3, R4",R_Axial_DIN0207_L6.3mm_D2.5mm_P10.16mm_Horizontal,7,470R,
"R10, R11, R12, R9",R_Axial_DIN0207_L6.3mm_D2.5mm_P10.16mm_Horizontal,4,47K,
"R15, R16, R8",R_Axial_DIN0207_L6.3mm_D2.5mm_P10.16mm_Horizontal,3,1K,
R17,R_Axial_DIN0207_L6.3mm_D2.5mm_P10.16mm_Horizontal,1,10K,
R18,R_Axial_DIN0207_L6.3mm_D2.5mm_P10.16mm_Horizontal,1,390R,
"R19, R21, R22, R23, R24, R25, R26, R27, R28, R29, R30, R31, R32, R33, R34, R35, R36, R37, R38, R39, R40",R_Axial_DIN0207_L6.3mm_D2.5mm_P10.16mm_Horizontal,21,3K9,
"R41, R42, R43, R44, R45, R46, R47, R48, R49, R50, R51, R52, R7",R_Axial_DIN0207_L6.3mm_D2.5mm_P10.16mm_Horizontal,13,1K8,
R5,R_Axial_DIN0207_L6.3mm_D2.5mm_P10.16mm_Horizontal,1,680R,
"R53, R54, R55, R56, R57, R58, R59, R6, R60, R61, R62, R63, R64",R_Axial_DIN0207_L6.3mm_D2.5mm_P10.16mm_Horizontal,13,100R,
RV1,Potentiometer_Bourns_3296W_Vertical,1,47K,
SW1,SW_PUSH-12mm,1,TUNE,
"U1, U4, U5, U6, U7",3 x PC817 on a DIP-16_W7.62mm_Socket_LongPads,5,PC817,
U2,TO-220-3_Horizontal_TabDown,1,L7805,
U3,DIP-16_W7.62mm_Socket_LongPads,1,MAX202CPE,
U8,TO-92_Inline,1,L78L09,
